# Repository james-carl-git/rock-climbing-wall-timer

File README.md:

# Rock Climbing Wall Timer
PCB for a timer on a rock climbing wall. Could be used for other timer functions

https://github.com/james-carl-git/rock-climbing-wall-timer/assets/78581339/d42f89ee-d3c8-4e2f-867b-dab42051f7c2

I built a rock wall for my niece and nephew. This repo is for the PCB I created that acts as a timer to measure how long it takes to climb the wall and determine who climbed it the fastest if 2 people are racing. 

Features:
- Simple PCB (2 layer, all through-hole) allows it to be easily hand soldered and you can use a CNC router to make it (this is what I did)
- Designed to be powered by batteries so has low power draw
- Buzzer/pizo speaker for an audible countdown before the timer starts (should be familiar if you have played those popular karting video games)
- 2x 7-segment LED arrays using 5mm LEDs, displays 0.0 to 9.9 seconds, and whole decimals after 10 seconds. 99s max time
- Inputs and outputs for an illuminated start button and 2 end buttons

I included CAD files for the 3d printed shroud I used separate the light from each segment.

Notes:
- LEDs in each digit are 3 LEDs wired in series and depending on what LEDs you use the voltage needed may be higher than the max voltage of the ATMega328P. As a result I have 2 separate inputs for power supply, one for the LEDs in the segmented display and one for the logic and the other LEDs/buzzer...etc.
- The current limiting resistors on the LEDs will be custom to what LEDs/supply voltage you choose.
- I used illuminated buttons for an arcade game as inputs
- Code is written in Arduino, I used the first Tlc5940 library by Paul Stoffregen when you search for 'tlc5940' in the library manager

Known issues:

The TLC5940 LED driver I used has a high idle current(couple ma) which would prevent you from running this on batteries. When I was debugging this issue I was surprised to find that the TLC5940 works even with its VCC pin floating and doesn't seem to draw as much current, although the batteries did not last as long as I was expecting so this needs to be investigated further. I added a jumper on the PCB to allow you to easily connect/disconnect VCC on the TLC5940. Easy solution would be to just power this from a wall wart which is what I ended up doing.

https://github.com/james-carl-git/rock-climbing-wall-timer/assets/78581339/c764d504-4ba1-4b2e-b260-3fb3670ae1da

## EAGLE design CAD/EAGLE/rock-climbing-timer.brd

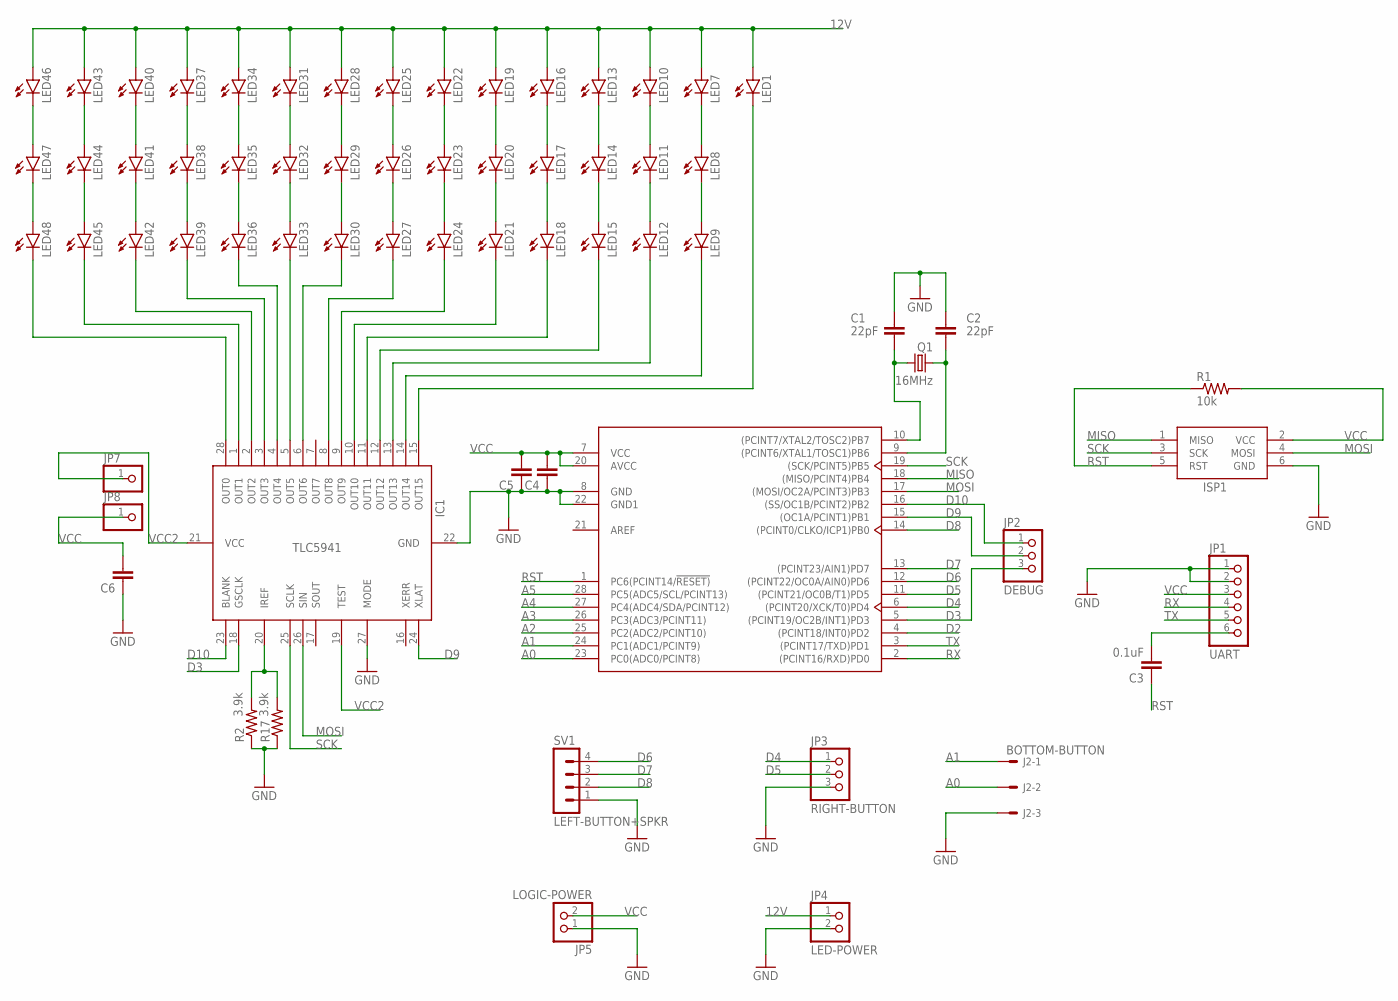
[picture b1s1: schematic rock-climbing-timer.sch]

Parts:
C1, C2: 22pF; C5B2.5
C3: 0.1uF; C5B2.5
C4, C5, C6: C5/2.5; C5B2.5
IC1: TLC5941NT; DIL28-3
ISP1: AVRISP-6; AVRISP
J2: BOTTOM-BUTTON; 6410-03
JP1: UART; 1X06
JP2: DEBUG; 1X03
JP3: RIGHT-BUTTON; 1X03
JP4: LED-POWER; 1X02
JP5: LOGIC-POWER; 1X02
JP7, JP8: PINHD-1X1CB; 1X01-CLEANBIG
LED1, LED7, LED8, LED9, LED10, LED11, LED12, LED13, LED14, LED15, LED16, LED17, LED18, LED19, LED20, LED21, LED22, LED23, LED24, LED25, LED26, LED27, LED28, LED29, LED30, LED31, LED32, LED33, LED34, LED35, LED36, LED37, LED38, LED39, LED40, LED41, LED42, LED43, LED44, LED45, LED46, LED47, LED48: LED5MM
Q1: 16MHz; HC49/S
R1: 10k; 0207/10
R2, R17: 3.9k; 0207/10
SV1: LEFT-BUTTON+SPKR; MA04-1
U1: ATMEGA328P-PU; DIP-28

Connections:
12V: JP4.1, LED1.A, LED7.A, LED10.A, LED13.A, LED16.A, LED19.A, LED22.A, LED25.A, LED28.A, LED31.A, LED34.A, LED37.A, LED40.A, LED43.A, LED46.A
A0: J2.2, U1.23 (PC0(ADC0/PCINT8))
A1: J2.1, U1.24 (PC1(ADC1/PCINT9))
A2: U1.25 (PC2(ADC2/PCINT10))
A3: U1.26 (PC3(ADC3/PCINT11))
A4: U1.27 (PC4(ADC4/SDA/PCINT12))
A5: U1.28 (PC5(ADC5/SCL/PCINT13))
D2: U1.4 ((PCINT18/INT0)PD2)
D3: IC1.18 (GSCLK), JP2.3, U1.5 ((PCINT19/OC2B/INT1)PD3)
D4: JP3.1, U1.6 ((PCINT20/XCK/T0)PD4)
D5: JP3.2, U1.11 ((PCINT21/OC0B/T1)PD5)
D6: SV1.4, U1.12 ((PCINT22/OC0A/AIN0)PD6)
D7: SV1.3, U1.13 ((PCINT23/AIN1)PD7)
D8: SV1.2, U1.14 ((PCINT0/CLKO/ICP1)PB0)
D9: IC1.24 (XLAT), JP2.2, U1.15 ((OC1A/PCINT1)PB1)
D10: IC1.23 (BLANK), JP2.1, U1.16 ((SS/OC1B/PCINT2)PB2)
GND: C1.1, C2.1, C4.1, C5.1, C6.1, IC1.22 (GND), IC1.27 (MODE), ISP1.6 (GND), J2.3, JP1.1, JP1.2, JP3.3, JP4.2, JP5.1, R2.1, R17.1, SV1.1, U1.8 (GND), U1.22 (GND1)
MISO: ISP1.1 (MISO), U1.18 ((MISO/PCINT4)PB4)
MOSI: IC1.26 (SIN), ISP1.4 (MOSI), U1.17 ((MOSI/OC2A/PCINT3)PB3)
unnamed: C1.2, Q1.2, U1.10 ((PCINT7/XTAL2/TOSC2)PB7)
unnamed: C2.2, Q1.1, U1.9 ((PCINT6/XTAL1/TOSC1)PB6)
unnamed: C3.2, JP1.6
unnamed: IC1.20 (IREF), R2.2, R17.2
unnamed: IC1.15 (OUT15), LED1.K (C)
unnamed: LED7.K (C), LED8.A
unnamed: LED8.K (C), LED9.A
unnamed: LED10.K (C), LED11.A
unnamed: LED11.K (C), LED12.A
unnamed: LED13.K (C), LED14.A
unnamed: LED14.K (C), LED15.A
unnamed: LED16.K (C), LED17.A
unnamed: LED17.K (C), LED18.A
unnamed: LED19.K (C), LED20.A
unnamed: LED20.K (C), LED21.A
unnamed: LED22.K (C), LED23.A
unnamed: LED23.K (C), LED24.A
unnamed: LED25.K (C), LED26.A
unnamed: LED26.K (C), LED27.A
unnamed: LED28.K (C), LED29.A
unnamed: LED29.K (C), LED30.A
unnamed: LED31.K (C), LED32.A
unnamed: LED32.K (C), LED33.A
unnamed: LED34.K (C), LED35.A
unnamed: LED35.K (C), LED36.A
unnamed: LED37.K (C), LED38.A
unnamed: LED38.K (C), LED39.A
unnamed: LED40.K (C), LED41.A
unnamed: LED41.K (C), LED42.A
unnamed: LED43.K (C), LED44.A
unnamed: LED44.K (C), LED45.A
unnamed: LED46.K (C), LED47.A
unnamed: LED47.K (C), LED48.A
unnamed: IC1.14 (OUT14), LED9.K (C)
unnamed: IC1.13 (OUT13), LED12.K (C)
unnamed: IC1.12 (OUT12), LED15.K (C)
unnamed: IC1.11 (OUT11), LED18.K (C)
unnamed: IC1.10 (OUT10), LED21.K (C)
unnamed: IC1.9 (OUT9), LED24.K (C)
unnamed: IC1.8 (OUT8), LED27.K (C)
unnamed: IC1.6 (OUT6), LED30.K (C)
unnamed: IC1.5 (OUT5), LED33.K (C)
unnamed: IC1.4 (OUT4), LED36.K (C)
unnamed: IC1.3 (OUT3), LED39.K (C)
unnamed: IC1.2 (OUT2), LED42.K (C)
unnamed: IC1.1 (OUT1), LED45.K (C)
unnamed: IC1.28 (OUT0), LED48.K (C)
RST: C3.1, ISP1.5 (RST), R1.1, U1.1 (PC6(PCINT14/!RESET))
RX: JP1.4, U1.2 ((PCINT16/RXD)PD0)
SCK: IC1.25 (SCLK), ISP1.3 (SCK), U1.19 ((SCK/PCINT5)PB5)
TX: JP1.5, U1.3 ((PCINT17/TXD)PD1)
VCC: C4.2, C5.2, C6.2, ISP1.2 (VCC), JP1.3, JP5.2, JP8.1, R1.2, U1.7 (VCC), U1.20 (AVCC)
VCC2: IC1.19 (TEST), IC1.21 (VCC), JP7.1

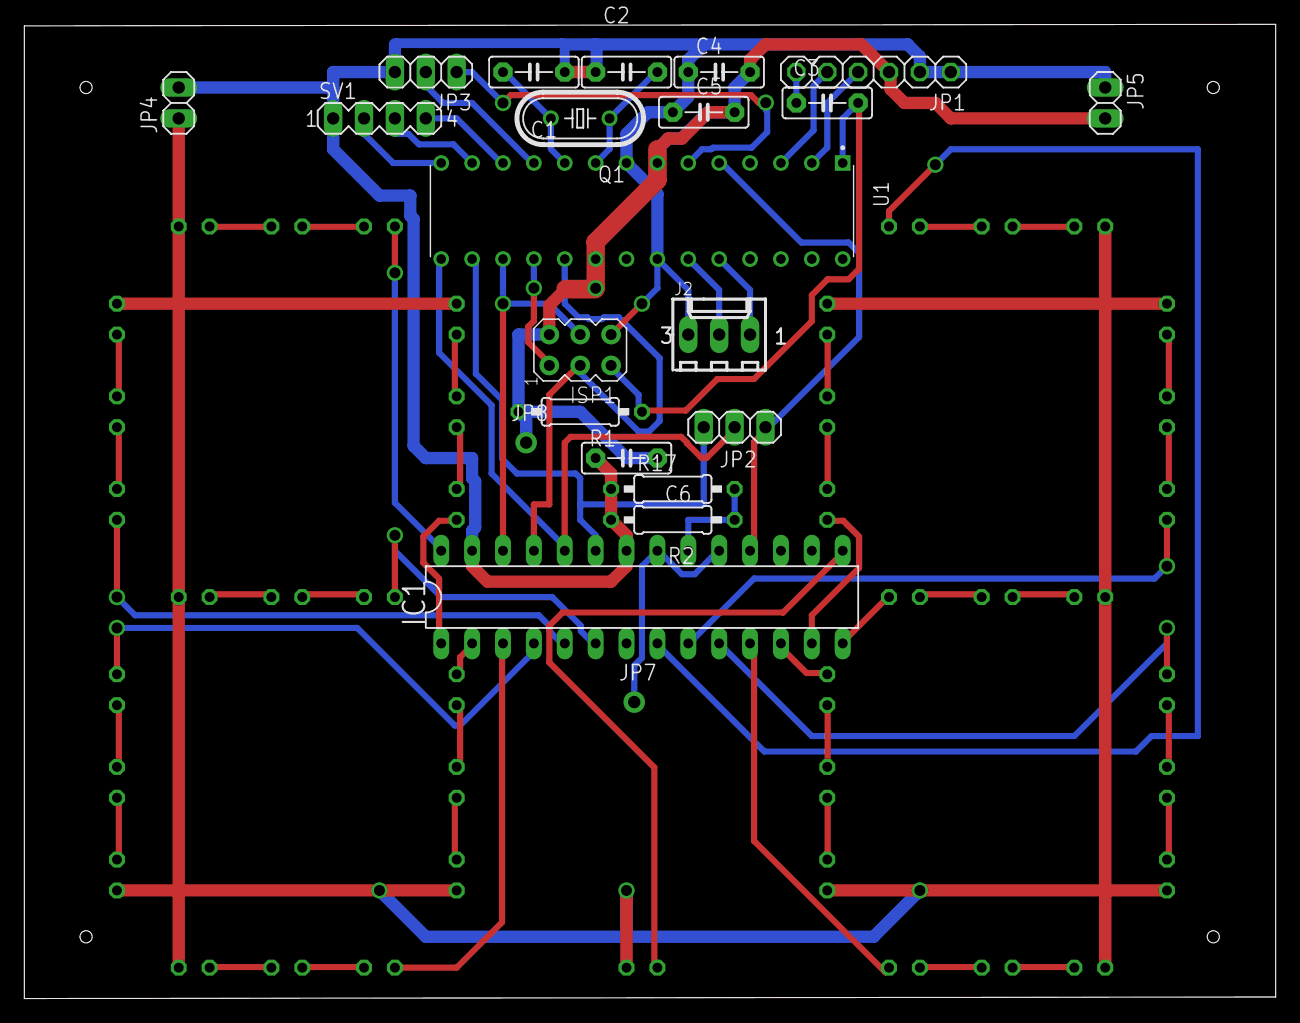
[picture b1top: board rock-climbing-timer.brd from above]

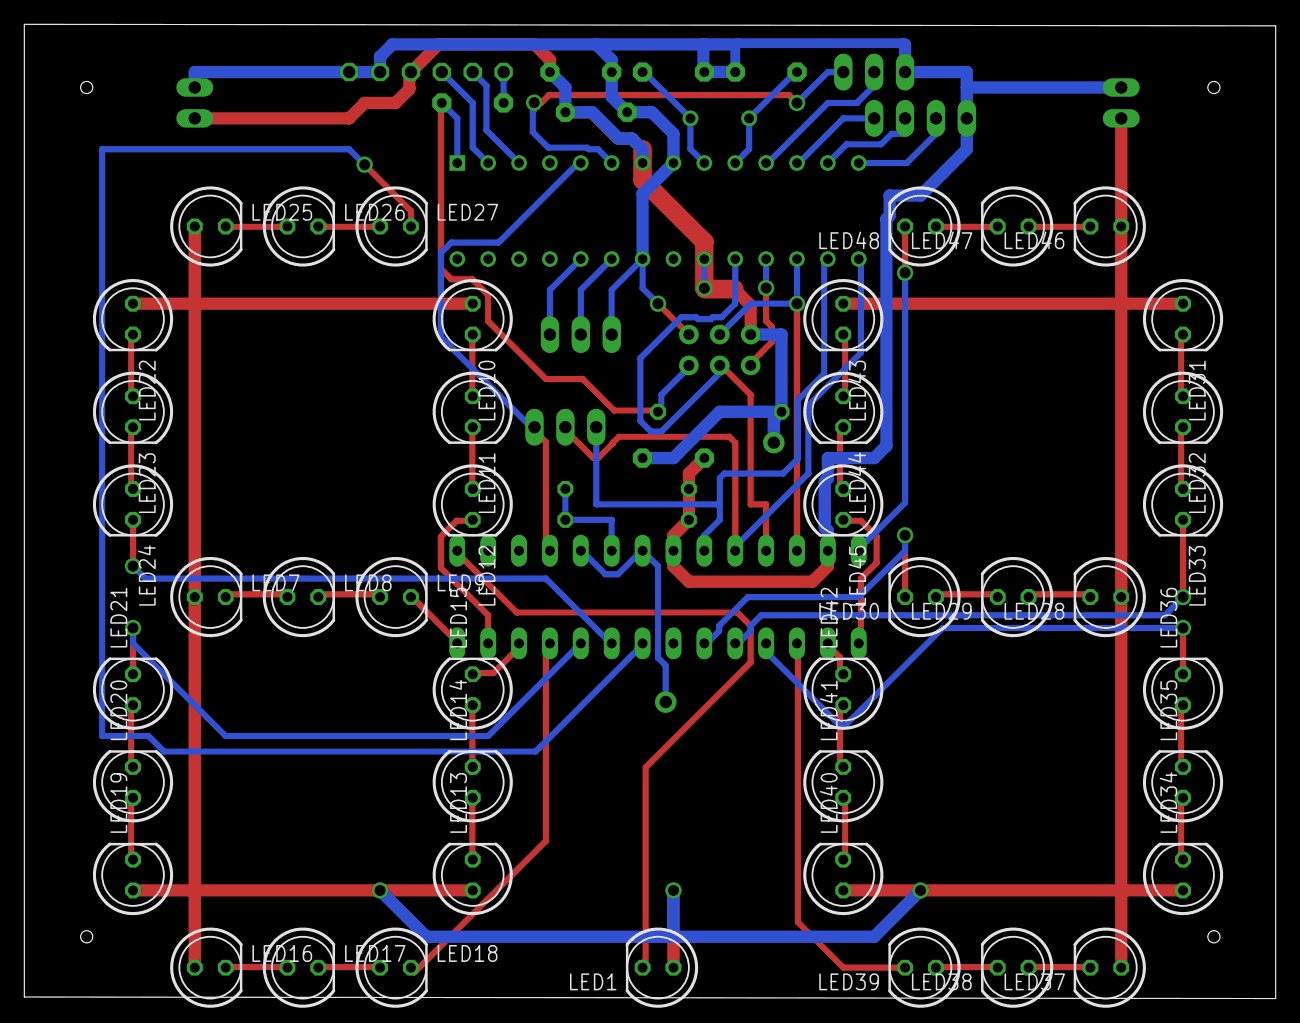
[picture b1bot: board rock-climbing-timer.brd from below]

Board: 2 copper layers, 102.9 x 80.1 mm, 65 parts (43 on the bottom side), 67 nets.

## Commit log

2023-12-31 Rename rockclimbingwall v6.f3d to CAD/shroud/rockclimbingwall v6.f3d
2023-12-31 Rename rock-climbing-timer.brd to CAD/EAGLE/rock-climbing-timer.brd
2023-12-31 Rename rock-climbing-timer.sch to CAD/EAGLE/rock-climbing-timer.sch
2023-12-31 Rename Screenshot 2023-12-30 235527.png to Media/Rock-climbing-wall-pcb
2023-12-31 Rename rock-climbing-wall-test.mp4 to Media/rock-climbing-wall-test.mp4
2023-12-31 Rename rock-climbing-wall.mp4 to Media/rock-climbing-wall.mp4
